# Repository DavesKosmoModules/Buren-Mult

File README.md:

# Buren-Mult

An active mult in Kosmo modular synth format

- 3 input 9 output active mult
- Normalized inputs can be 1 in 9 out, 3 in 3 outs or 2 in 3 out + 6 out
- Original concept was to allow patching of V/oct, Gate & velocity from a sequencer

Contained are schematics & gerber files for pcb fabrication of both electrical and front panel. This is sutiable for entry level however a basic level of electronics, soldering, fault finding, and some basic tools are required.

If you wish to edit in ki-cad the following dependencies are required

https://gitlab.com/rsholmes/Kosmo_panel
 
https://gitlab.com/rsholmes/aoKicad

[Schematic](/Docs/Buren-Mult-Schematic.pdf)

[BOM](Docs/Buren-Mult-BOM.pdf)

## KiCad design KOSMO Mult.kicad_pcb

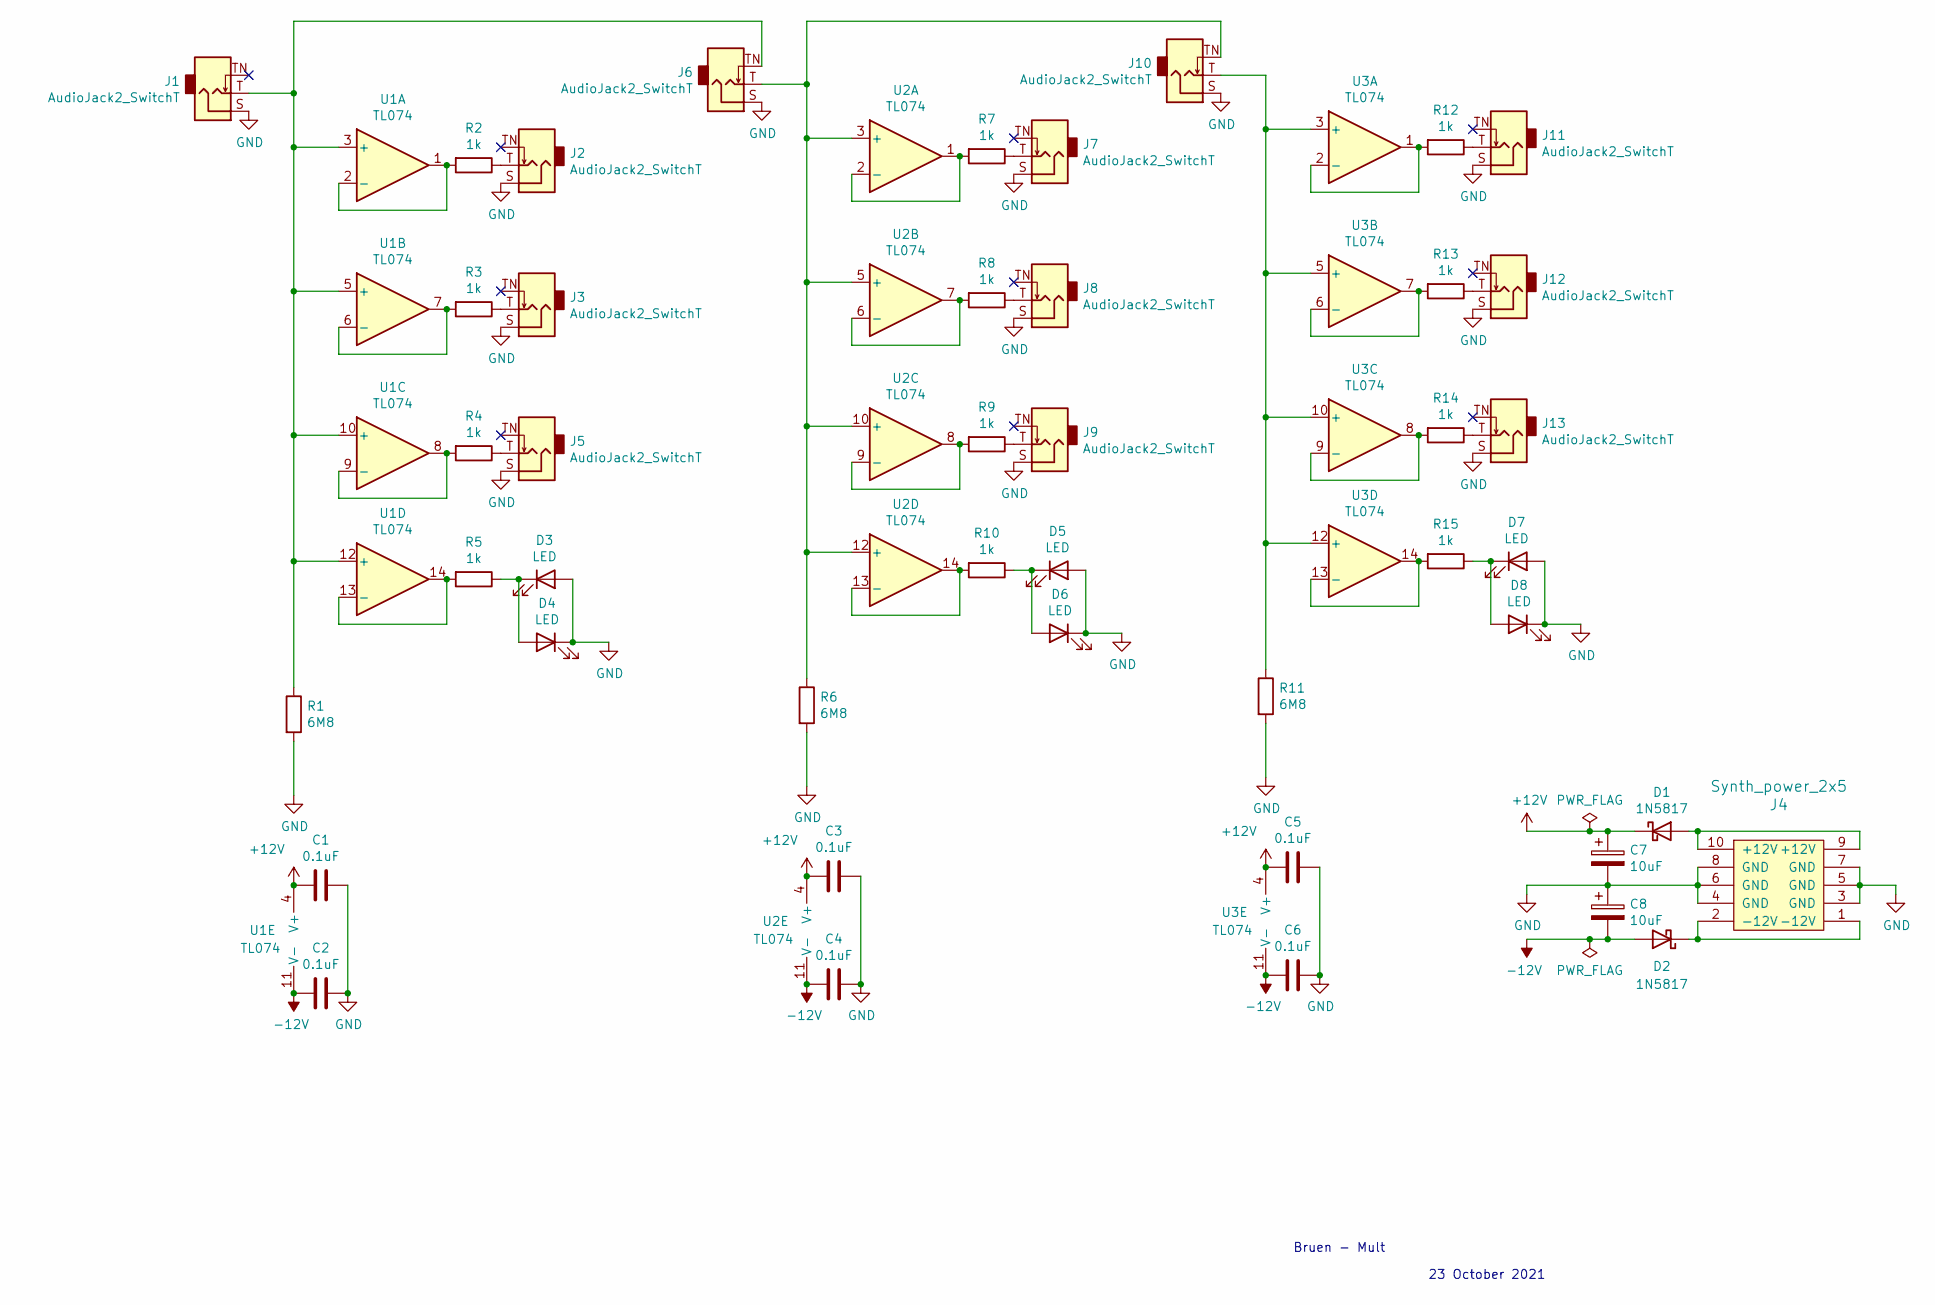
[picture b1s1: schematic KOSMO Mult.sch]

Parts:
C1, C2, C3, C4, C5, C6: 0.1uF; C_Disc_D3.0mm_W1.6mm_P2.50mm
C7, C8: 10uF; CP_Radial_D6.3mm_P2.50mm
D1, D2: 1N5817; D_DO-41_SOD81_P10.16mm_Horizontal
D3, D4, D5, D6, D7, D8: LED; LED_D5.0mm
J1, J2, J3, J5, J6, J7, J8, J9, J10, J11, J12, J13: AudioJack2_SwitchT; Jack_6.35mm_PJ_629HAN
J4: Synth_power_2x5; Power_Header
R1, R6, R11: 6M8; R_Axial_DIN0207_L6.3mm_D2.5mm_P10.16mm_Horizontal
R2, R3, R4, R5, R7, R8, R9, R10, R12, R13, R14, R15: 1k; R_Axial_DIN0207_L6.3mm_D2.5mm_P10.16mm_Horizontal
U1, U2, U3: TL074; DIP-14_W7.62mm_Socket_LongPads

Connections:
+12V: C1.2, C3.2, C5.2, C7.1, D1.1 (K), U1.4 (V+), U2.4 (V+), U3.4 (V+)
-12V: C2.2, C4.2, C6.2, C8.2, D2.2 (A), U1.11 (V-), U2.11 (V-), U3.11 (V-)
GND: C1.1, C2.1, C3.1, C4.1, C5.1, C6.1, C7.2, C8.1, D3.2 (A), D4.1 (K), D5.2 (A), D6.1 (K), D7.2 (A), D8.1 (K), J1.S, J2.S, J3.S, J4.3 (GND), J4.4 (GND), J4.5 (GND), J4.6 (GND), J4.7 (GND), J4.8 (GND), J5.S, J6.S, J7.S, J8.S, J9.S, J10.S, J11.S, J12.S, J13.S, R1.2, R6.2, R11.2
unnamed: D1.2 (A), J4.9 (+12V), J4.10 (+12V)
unnamed: D2.1 (K), J4.1 (-12V), J4.2 (-12V)
unnamed: D3.1 (K), D4.2 (A), R5.1
unnamed: D5.1 (K), D6.2 (A), R10.1
unnamed: D7.1 (K), D8.2 (A), R15.1
unnamed: J1.T, J6.TN, R1.1, U1.3 (+), U1.5 (+), U1.10 (+), U1.12 (+)
unnamed: J2.T, R2.1
unnamed: J3.T, R3.1
unnamed: J5.T, R4.1
unnamed: J7.T, R7.1
unnamed: J8.T, R8.1
unnamed: J9.T, R9.1
unnamed: J10.T, R11.1, U3.3 (+), U3.5 (+), U3.10 (+), U3.12 (+)
unnamed: J6.T, J10.TN, R6.1, U2.3 (+), U2.5 (+), U2.10 (+), U2.12 (+)
unnamed: J11.T, R12.1
unnamed: J12.T, R13.1
unnamed: J13.T, R14.1
unnamed: R2.2, U1.1, U1.2 (-)
unnamed: R3.2, U1.6 (-), U1.7
unnamed: R4.2, U1.8, U1.9 (-)
unnamed: R5.2, U1.13 (-), U1.14
unnamed: R7.2, U2.1, U2.2 (-)
unnamed: R8.2, U2.6 (-), U2.7
unnamed: R9.2, U2.8, U2.9 (-)
unnamed: R10.2, U2.13 (-), U2.14
unnamed: R12.2, U3.1, U3.2 (-)
unnamed: R13.2, U3.6 (-), U3.7
unnamed: R14.2, U3.8, U3.9 (-)
unnamed: R15.2, U3.13 (-), U3.14

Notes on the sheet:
Bruen - Mult
23 October 2021

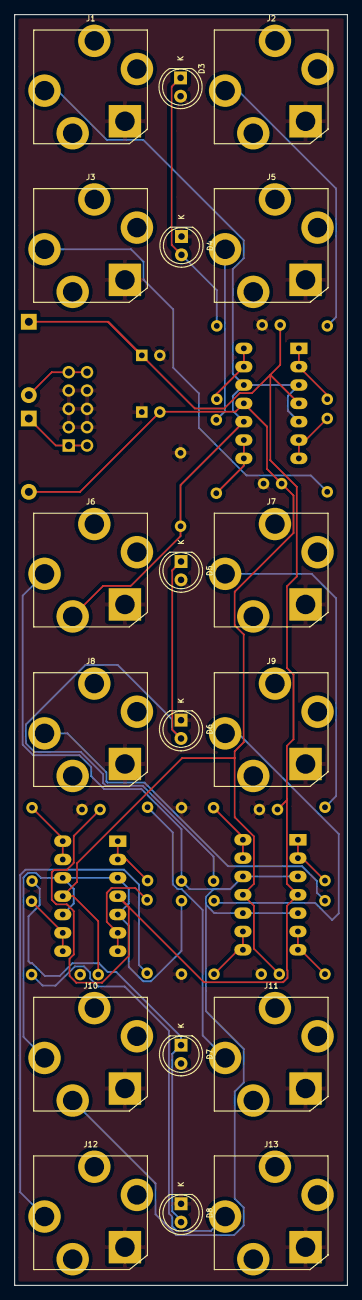
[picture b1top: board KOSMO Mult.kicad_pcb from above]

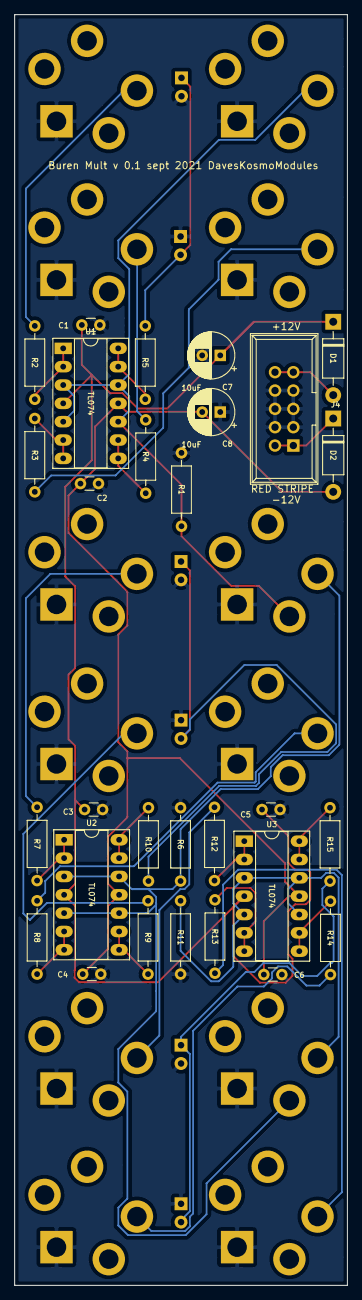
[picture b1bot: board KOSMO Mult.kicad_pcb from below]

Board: 2 copper layers, 46.1 x 176.0 mm, 47 parts (29 on the bottom side), 32 nets.

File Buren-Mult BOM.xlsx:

Id | Designator | Package | Quantity | Designation
1 | C1,C2,C3,C4,C5,C6 | C_Disc_D3.0mm_W1.6mm_P2.50mm | 6 | 0.1uF
2 | C7,C8 | CP_Radial_D6.3mm_P2.50mm | 2 | 10uF
3 | D1,D2 | D_DO-41_SOD81_P10.16mm_Horizontal | 2 | 1N5817
4 | D3,D4,D5,D6,D7,D8 | LED_D5.0mm | 6 | LED
5 | J1,J2,J3,J5,J6,J7,J8,J9,J10,J11,J12,J13 | Jack_6.35mm_PJ_629HAN | 12 | AudioJack2_SwitchT
6 | J4 | Power_Header | 1 | Synth_power_2x5
7 | R1,R6,R11 | R_Axial_DIN0207_L6.3mm_D2.5mm_P10.16mm_Horizontal | 3 | 6M8
8 | R2,R3,R4,R5,R7,R8,R9,R10,R12,R13,R14,R15 | R_Axial_DIN0207_L6.3mm_D2.5mm_P10.16mm_Horizontal | 12 | 1k
9 | U1,U2,U3 | DIP-14_W7.62mm_Socket_LongPads | 3 | TL074

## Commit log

2021-10-23 Initial
2021-10-23 updated readme links
2021-10-23 Readme links
2021-10-23 Readme link again
2021-10-23 scale photo
2021-10-23 Readme dependencies
2024-10-25 Update README.md
    update links to Analog output R Holmes repo
